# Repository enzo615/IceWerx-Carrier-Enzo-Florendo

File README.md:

# IceWerx-Carrier-Enzo-Florendo
apu engr240 lab weeks 1-4

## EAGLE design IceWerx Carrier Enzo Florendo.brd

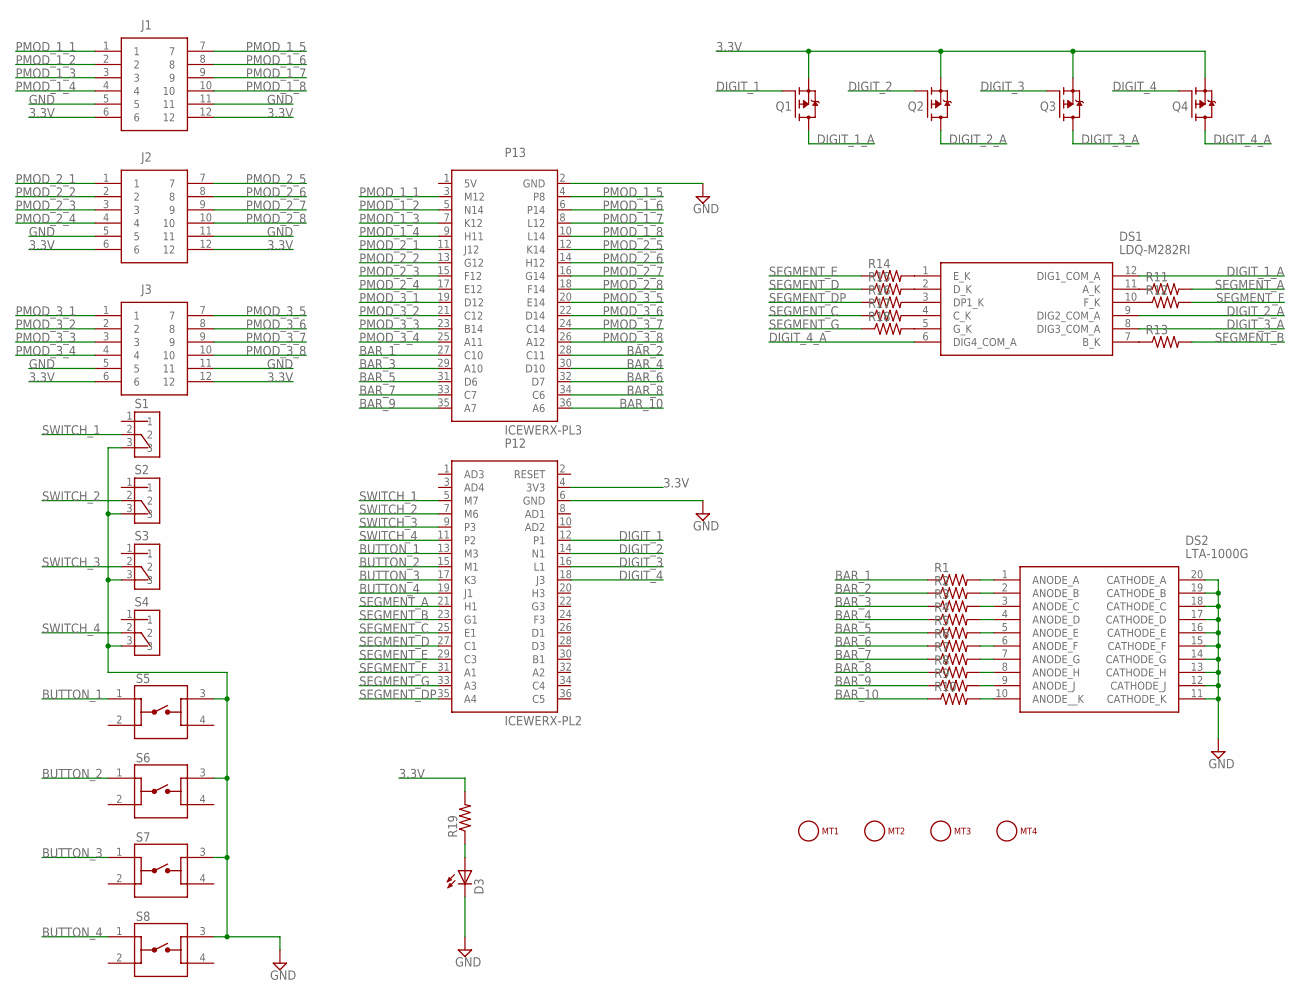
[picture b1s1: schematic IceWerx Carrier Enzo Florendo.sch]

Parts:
D3: LED5MM
DS1: LDQ-M282RI; LDQM282RI
DS2: LTA-1000G; DIPS762W50P254L2527H825Q20N
J1, J2, J3: PMOD-SOCKET-FOR-HOST-BOARD
MT1, MT2, MT3, MT4: MOUNTING_HOLE-125_250_ROUND; MT_125_250
P12: ICEWERX-PL2; TE_4-1734506-1
P13: ICEWERX-PL3; TE_4-1734506-1
Q1, Q2, Q3, Q4: NX2301P; SOT95P230X110-3N
R1, R2, R3, R4, R5, R6, R7, R8, R9, R10, R11, R12, R13, R14, R15, R16, R17, R18, R19: R-US_0204/5; 0204/5
S1, S2, S3, S4: OS102011MS2QN1; SW_OS102011MS2QN1
S5, S6, S7, S8: 1825910-7; SW_1825910-7

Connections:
3.3V: J1.6, J1.12, J2.6, J2.12, J3.6, J3.12, P12.4 (3V3), Q1.2 (S), Q2.2 (S), Q3.2 (S), Q4.2 (S), R19.2
BAR_1: P13.27 (C10), R1.1
BAR_2: P13.28 (C11), R2.1
BAR_3: P13.29 (A10), R3.1
BAR_4: P13.30 (D10), R4.1
BAR_5: P13.31 (D6), R5.1
BAR_6: P13.32 (D7), R6.1
BAR_7: P13.33 (C7), R7.1
BAR_8: P13.34 (C6), R8.1
BAR_9: P13.35 (A7), R9.1
BAR_10: P13.36 (A6), R10.1
BUTTON_1: P12.13 (M3), S5.1
BUTTON_2: P12.15 (M1), S6.1
BUTTON_3: P12.17 (K3), S7.1
BUTTON_4: P12.19 (J1), S8.1
DIGIT_1: P12.12 (P1), Q1.1 (G)
DIGIT_1_A: DS1.12 (DIG1_COM_A), Q1.3 (D)
DIGIT_2: P12.14 (N1), Q2.1 (G)
DIGIT_2_A: DS1.9 (DIG2_COM_A), Q2.3 (D)
DIGIT_3: P12.16 (L1), Q3.1 (G)
DIGIT_3_A: DS1.8 (DIG3_COM_A), Q3.3 (D)
DIGIT_4: P12.18 (J3), Q4.1 (G)
DIGIT_4_A: DS1.6 (DIG4_COM_A), Q4.3 (D)
GND: D3.K (C), DS2.11 (CATHODE_K), DS2.12 (CATHODE_J), DS2.13 (CATHODE_H), DS2.14 (CATHODE_G), DS2.15 (CATHODE_F), DS2.16 (CATHODE_E), DS2.17 (CATHODE_D), DS2.18 (CATHODE_C), DS2.19 (CATHODE_B), DS2.20 (CATHODE_A), J1.5, J1.11, J2.5, J2.11, J3.5, J3.11, P12.6 (GND), P13.2 (GND), S1.3, S2.3, S3.3, S4.3, S5.3, S6.3, S7.3, S8.3
unnamed: D3.A, R19.1
unnamed: DS2.1 (ANODE_A), R1.2
unnamed: DS2.2 (ANODE_B), R2.2
unnamed: DS2.3 (ANODE_C), R3.2
unnamed: DS2.4 (ANODE_D), R4.2
unnamed: DS2.5 (ANODE_E), R5.2
unnamed: DS2.6 (ANODE_F), R6.2
unnamed: DS2.7 (ANODE_G), R7.2
unnamed: DS2.8 (ANODE_H), R8.2
unnamed: DS2.9 (ANODE_J), R9.2
unnamed: DS2.10 (ANODE__K), R10.2
unnamed: DS1.11 (A_K), R11.1
unnamed: DS1.10 (F_K), R12.1
unnamed: DS1.7 (B_K), R13.1
unnamed: DS1.1 (E_K), R14.2
unnamed: DS1.2 (D_K), R15.2
unnamed: DS1.3 (DP1_K), R16.2
unnamed: DS1.4 (C_K), R17.2
unnamed: DS1.5 (G_K), R18.2
PMOD_1_1: J1.1, P13.3 (M12)
PMOD_1_2: J1.2, P13.5 (N14)
PMOD_1_3: J1.3, P13.7 (K12)
PMOD_1_4: J1.4, P13.9 (H11)
PMOD_1_5: J1.7, P13.4 (P8)
PMOD_1_6: J1.8, P13.6 (P14)
PMOD_1_7: J1.9, P13.8 (L12)
PMOD_1_8: J1.10, P13.10 (L14)
PMOD_2_1: J2.1, P13.11 (J12)
PMOD_2_2: J2.2, P13.13 (G12)
PMOD_2_3: J2.3, P13.15 (F12)
PMOD_2_4: J2.4, P13.17 (E12)
PMOD_2_5: J2.7, P13.12 (K14)
PMOD_2_6: J2.8, P13.14 (H12)
PMOD_2_7: J2.9, P13.16 (G14)
PMOD_2_8: J2.10, P13.18 (F14)
PMOD_3_1: J3.1, P13.19 (D12)
PMOD_3_2: J3.2, P13.21 (C12)
PMOD_3_3: J3.3, P13.23 (B14)
PMOD_3_4: J3.4, P13.25 (A11)
PMOD_3_5: J3.7, P13.20 (E14)
PMOD_3_6: J3.8, P13.22 (D14)
PMOD_3_7: J3.9, P13.24 (C14)
PMOD_3_8: J3.10, P13.26 (A12)
SEGMENT_A: P12.21 (H1), R11.2
SEGMENT_B: P12.23 (G1), R13.2
SEGMENT_C: P12.25 (E1), R17.1
SEGMENT_D: P12.27 (C1), R15.1
SEGMENT_DP: P12.35 (A4), R16.1
SEGMENT_E: P12.29 (C3), R14.1
SEGMENT_F: P12.31 (A1), R12.2
SEGMENT_G: P12.33 (A3), R18.1
SWITCH_1: P12.5 (M7), S1.2
SWITCH_2: P12.7 (M6), S2.2
SWITCH_3: P12.9 (P3), S3.2
SWITCH_4: P12.11 (P2), S4.2

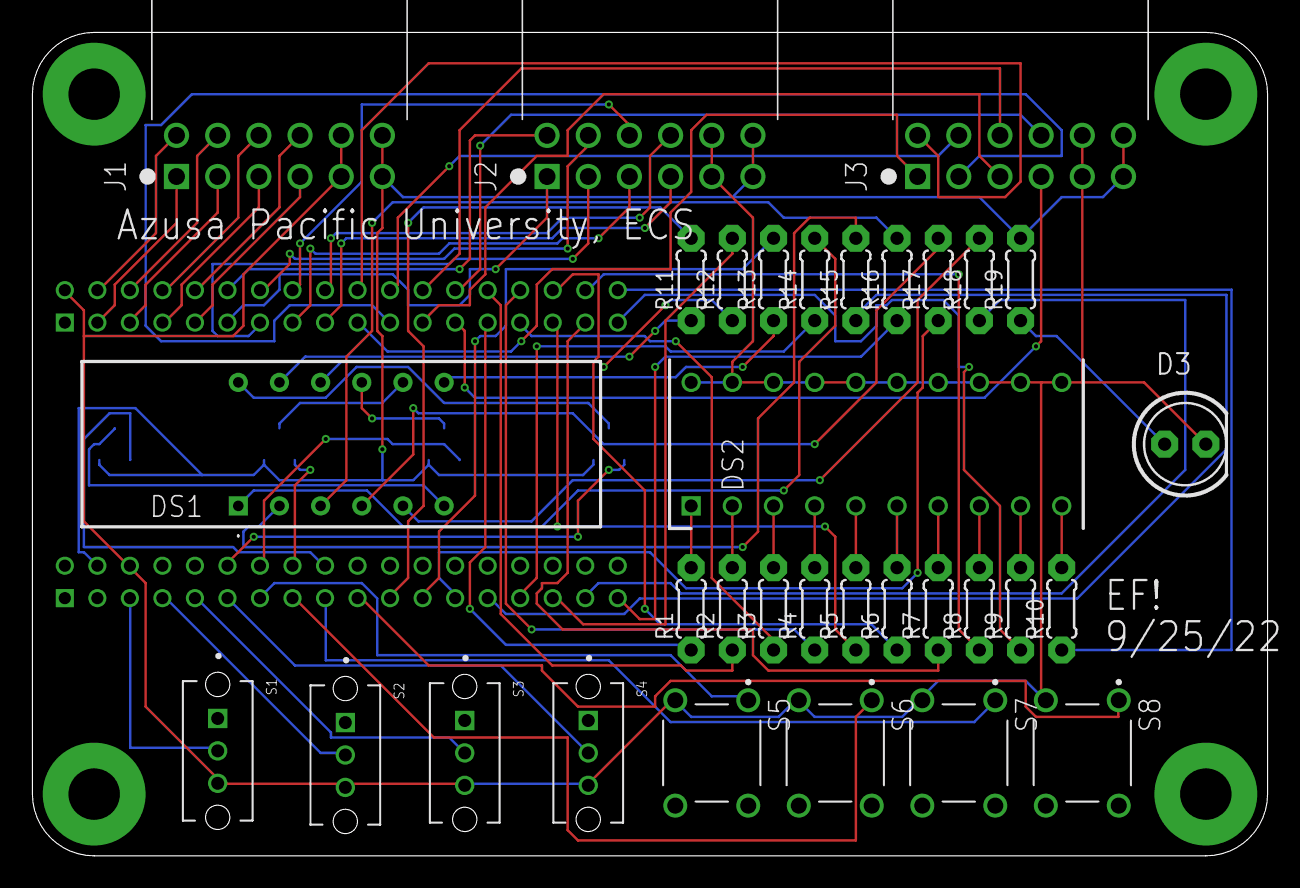
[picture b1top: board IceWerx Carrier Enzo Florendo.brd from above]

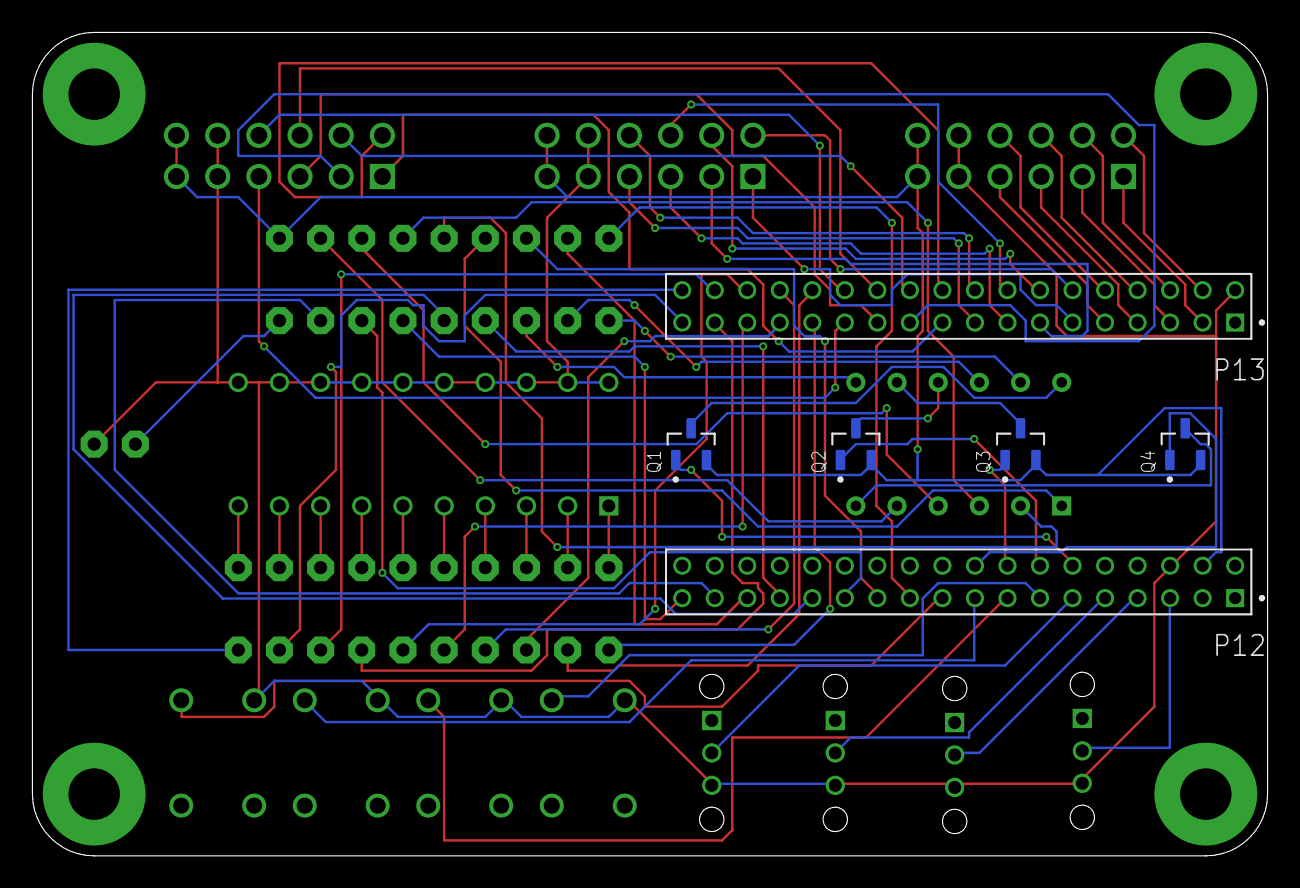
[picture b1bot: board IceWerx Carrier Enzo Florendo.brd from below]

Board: 2 copper layers, 76.2 x 50.8 mm, 43 parts (6 on the bottom side), 79 nets.
